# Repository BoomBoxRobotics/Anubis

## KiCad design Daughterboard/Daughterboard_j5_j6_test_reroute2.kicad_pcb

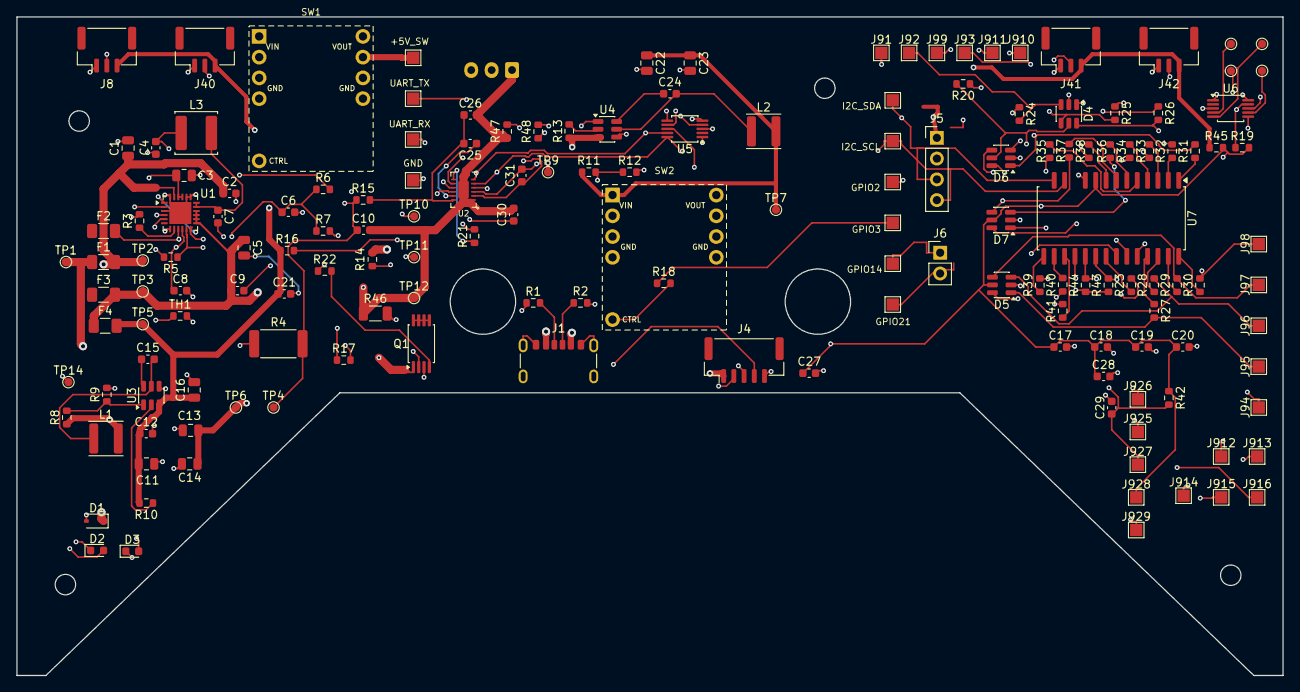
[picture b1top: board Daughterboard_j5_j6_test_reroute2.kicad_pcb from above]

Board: 4 copper layers, 155.0 x 80.6 mm, 160 parts (0 on the bottom side), 100 nets.

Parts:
C1: 10uF 10V X5R; C_0805_2012Metric
C2, C17, C19, C27, C29: 100nF 10V X7R; C_0603_1608Metric
C3, C5, C13, C14, C22, C23: 22uF 16V X5R; C_0805_2012Metric
C4, C7, C9, C10, C12, C15, C21, C24, C25, C26, C31: 100nF 16V X7R; C_0603_1608Metric
C6: 4.7uF 6.3V X5R; C_0603_1608Metric
C8: 100nF 10V X7R DNP; C_0603_1608Metric
C11, C16: 10uF 16V X5R; C_0805_2012Metric
C18, C20, C28: 1uF 10V X5R; C_0603_1608Metric
C30: 2.2uF 10V X5R; C_0603_1608Metric
D1: PESD5V0S1BA 5V VBUS TVS; D_SOD-323
D2: LED green; LED_0603_1608Metric
D3: LED blue; LED_0603_1608Metric
D4, D5, D6, D7: SRV05-4.TCT / C13612 4ch ESD; SOT-23-6
F1: BSMD1206-200-16V 2A hold polyfuse; Fuse_1206_3216Metric
F2: BSMD1206-200-16V cell1 PTC; Fuse_1206_3216Metric
F3: BSMD1206-200-16V cell2 PTC; Fuse_1206_3216Metric
F4: BSMD1206-200-16V system fuse; Fuse_1206_3216Metric
J1: USB-C 5V Sink; USB_C_Receptacle_GCT_USB4125-xx-x_6P_TopMnt_Horizontal
J4: BM05B-GHS-TBT UART JST-GH top-entry 1.25mm; JST_GH_BM05B-GHS-TBT_1x05-1MP_P1.25mm_Vertical
J5: I2C 2.54mm through-hole male header; PinHeader_1x04_P2.54mm_Vertical
J6: Deep sleep 2.54mm through-hole header; PinHeader_1x02_P2.54mm_Vertical
J7: 2S balance input JST-XH side-entry; JST_XH_S3B-XH-A_1x03_P2.50mm_Horizontal
J8: Left gimbal A JST-GH 1.25mm; JST_GH_BM03B-GHS-TBT_1x03-1MP_P1.25mm_Vertical
J30: J3P Hosyond +5V_SW solder pad; TestPoint_Pad_1.5x1.5mm
J31: J3A Hosyond UART_TX solder pad; TestPoint_Pad_1.5x1.5mm
J32: J3B Hosyond UART_RX solder pad; TestPoint_Pad_1.5x1.5mm
J33: J3C Hosyond I2C_SDA solder pad; TestPoint_Pad_1.5x1.5mm
J34: J3D Hosyond I2C_SCL solder pad; TestPoint_Pad_1.5x1.5mm
J35: J3E Hosyond GPIO2 solder pad; TestPoint_Pad_1.5x1.5mm
J36: J3F Hosyond GPIO3 solder pad; TestPoint_Pad_1.5x1.5mm
J37: J3G Hosyond GPIO14 solder pad; TestPoint_Pad_1.5x1.5mm
J38: J3H Hosyond GPIO21 solder pad; TestPoint_Pad_1.5x1.5mm
J39: J3I Hosyond GND solder pad; TestPoint_Pad_1.5x1.5mm
J40: Left gimbal B JST-GH 1.25mm; JST_GH_BM03B-GHS-TBT_1x03-1MP_P1.25mm_Vertical
J41: Right gimbal A JST-GH 1.25mm; JST_GH_BM03B-GHS-TBT_1x03-1MP_P1.25mm_Vertical
J42: Right gimbal B JST-GH 1.25mm; JST_GH_BM03B-GHS-TBT_1x03-1MP_P1.25mm_Vertical
J91: MCP23017 GPA0 solder pad; TestPoint_Pad_1.5x1.5mm
J92: MCP23017 GPA1 solder pad; TestPoint_Pad_1.5x1.5mm
J93: MCP23017 GPA2 solder pad; TestPoint_Pad_1.5x1.5mm
J94: MCP23017 GPA3 solder pad; TestPoint_Pad_1.5x1.5mm
J95: MCP23017 GPA4 solder pad; TestPoint_Pad_1.5x1.5mm
J96: MCP23017 GPA5 solder pad; TestPoint_Pad_1.5x1.5mm
J97: MCP23017 GPA6 solder pad; TestPoint_Pad_1.5x1.5mm
J98: MCP23017 GPA7 solder pad; TestPoint_Pad_1.5x1.5mm
J99: MCP23017 GPB0 solder pad; TestPoint_Pad_1.5x1.5mm
J910: MCP23017 GPB1 solder pad; TestPoint_Pad_1.5x1.5mm
J911: MCP23017 GPB2 solder pad; TestPoint_Pad_1.5x1.5mm
J912: MCP23017 GPB3 solder pad; TestPoint_Pad_1.5x1.5mm
J913: MCP23017 GPB4 solder pad; TestPoint_Pad_1.5x1.5mm
J914: MCP23017 GPB5 solder pad; TestPoint_Pad_1.5x1.5mm
J915: MCP23017 GPB6 solder pad; TestPoint_Pad_1.5x1.5mm
J916: MCP23017 GPB7 solder pad; TestPoint_Pad_1.5x1.5mm
J925: MCP23017 INTA solder pad; TestPoint_Pad_1.5x1.5mm
J926: MCP23017 INTB solder pad; TestPoint_Pad_1.5x1.5mm
J927: MCP23017 RESET solder pad; TestPoint_Pad_1.5x1.5mm
J928: MCP23017 +3V3_SW solder pad; TestPoint_Pad_1.5x1.5mm
J929: MCP23017 GND solder pad; TestPoint_Pad_1.5x1.5mm
L1: 4.7uH >=3A sat; L_APV_ANR4020
L2: 4.7uH >=2A sat; L_APV_ANR4020
L3: ANR5040T1R0M 1uH; L_APV_ANR5040
Q1: PT8810 dual N-MOSFET; TSSOP-8_4.4x3mm_P0.65mm
R1, R2: 5.1k 1%; R_0603_1608Metric
R3: 806R 1% ILIM; R_0603_1608Metric
R4: 43R 1W CBSET; R_2512_6332Metric
R5: 10k 1%; R_0603_1608Metric
R6, R7: 2.2k; R_0603_1608Metric
R8: 523k 1%; R_0603_1608Metric
R9, R12: 100k 1%; R_0603_1608Metric
R10, R13: 100k; R_0603_1608Metric
R11: 316k 1%; R_0603_1608Metric
R14, R15: 470R 1%; R_0603_1608Metric
R16, R21, R22, R23, R24, R25, R26, R27, R28, R29, R30, R31, R32, R33, R34, R35, R36, R37, R38, R47, R48: 100R; R_0603_1608Metric
R17, R18: 330R; R_0603_1608Metric
R19, R20: 4.7k; R_0603_1608Metric
R39, R40, R41, R45: 0R; R_0603_1608Metric
R42, R43, R44: 10k; R_0603_1608Metric
R46: 2mR 1% 50ppm; R_1206_3216Metric
SW1: Pololu #2808 5V switch; Pololu_2808_Raised_Header
SW2: Pololu #2808 3V3 switch; Pololu_2808_Raised_Header
TH1: NCP18XH103F03RB 10k NTC; R_0603_1608Metric
TP1: USB_VBUS test pad; TestPoint_Pad_D1.0mm
TP2: CHG_IN test pad; TestPoint_Pad_D1.0mm
TP3: PACK_P test pad; TestPoint_Pad_D1.0mm
TP4: CELL_MID test pad; TestPoint_Pad_D1.0mm
TP5: BAT_SYS test pad; TestPoint_Pad_D1.0mm
TP6: +5V test pad; TestPoint_Pad_D1.0mm
TP7: +3V3 test pad; TestPoint_Pad_D1.0mm
TP9: +3V3_SW test pad; TestPoint_Pad_D1.0mm
TP10: CHG_STAT test pad; TestPoint_Pad_D1.0mm
TP11: PG_STAT test pad; TestPoint_Pad_D1.0mm
TP12: BATT_RAW_N test pad; TestPoint_Pad_D1.0mm
TP14: GND test pad; TestPoint_Pad_D1.0mm
TP15: AIN4 test pad; TestPoint_Pad_D1.0mm
TP16: AIN5 test pad; TestPoint_Pad_D1.0mm
TP17: AIN6 test pad; TestPoint_Pad_D1.0mm
TP18: AIN7 test pad; TestPoint_Pad_D1.0mm
U1: BQ25887RGER 2S charger; Texas_RGE0024H_VQFN-24-1EP_4x4mm_P0.5mm_EP2.7x2.7mm
U2: BQ28Z610DRZR-R1; BQ28Z610_DRZ0012A_12SON_2.5x4mm_P0.5mm
U3: AP63200WU-7 5V Buck; TSOT-23-6
U4: AP63200WU-7 3V3 Buck; TSOT-23-6
U5: ADS1115IDGSR 0x48; TSSOP-10_3x3mm_P0.5mm
U6: ADS1115IDGSR 0x49; TSSOP-10_3x3mm_P0.5mm
U7: MCP23017-E/SO; SOIC-28W_7.5x17.9mm_P1.27mm_NoPads11_14

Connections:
+3V3: C22.1, C23.1, L2.2, R11.1, SW2.1, TP7.1
+3V3_SW: J5.1, J8.3, J40.3, J41.3, J42.3, R45.1, SW2.2, TP9.1
+3V3_SW_LOGIC: C17.1, C18.1, C19.1, C20.1, C27.1, C28.1, D4.5, D5.5, D6.5, D7.5, J928.1, R19.2, R20.2, R42.1, R43.1, R44.1, R45.2, U5.8, U6.1, U6.8, U7.9
+5V: C13.1, C14.1, L1.2, R8.1, SW1.1, TP6.1
+5V_SW: J4.1, J30.1, SW1.2
AIN0: J8.2, U5.4
AIN1: J40.2, U5.5
AIN2: J41.2, U5.6
AIN3: J42.2, U5.7
AIN4: TP15.1, U6.4
AIN5: TP16.1, U6.5
AIN6: TP17.1, U6.6
AIN7: TP18.1, U6.7
BATT_RAW_N: C10.2, C26.2, C30.2, J7.1, Q1.1, R46.1, R47.1, TP12.1, U2.1, U2.13
BAT_SYS: C11.1, C12.1, C16.1, C21.1, F4.2, R10.2, R13.2, R16.1, TP5.1, U3.3, U4.3
BQ_CHG: R22.1, U2.9
BQ_DSG: R21.1, U2.7
BQ_PACK: R16.2, U2.8
BQ_PBI: C30.1, U2.10
BQ_SRN: C31.1, R47.2, U2.2
BQ_SRP: C31.2, R48.2, U2.3
BST_3V3: C24.1, U4.6
BST_5V: C15.1, U3.6
BTST: C7.1, U1.12
CBSET: C8.1, R4.1, U1.10
CC1: J1.A5, R1.1
CC2: J1.B5, R2.1
CELL_MID: C9.2, C10.1, F2.2, J7.2, R4.2, R15.1, TP4.1, U1.9
CHG_IN: C1.1, C2.1, D1.1, F1.2, TP2.1, U1.23
CHG_STAT: D2.2, TP10.1, U1.2
CHG_SW: C7.2, L3.2, U1.17, U1.18
CO_GATE: Q1.4, R22.2
CTRL_3V3_SW: R18.2, SW2.4
CTRL_5V_SW: R17.2, SW1.4
DO_GATE: Q1.2, R21.2
EN_3V3: R13.1, U4.2
EN_5V: R10.1, U3.2
EXP_GPA0: D4.1, J91.1, R23.2
EXP_GPA1: D4.3, J92.1, R24.2
EXP_GPA2: D4.4, J93.1, R25.2
EXP_GPA3: D4.6, J94.1, R26.2
EXP_GPA4: D5.1, J95.1, R27.2
EXP_GPA5: D5.3, J96.1, R28.2
EXP_GPA6: D5.4, J97.1, R29.2
EXP_GPA7: D5.6, J98.1, R30.2
EXP_GPB0: D6.1, J99.1, R31.2
EXP_GPB1: D6.3, J910.1, R32.2
EXP_GPB2: D6.4, J911.1, R33.2
EXP_GPB3: D6.6, J912.1, R34.2
EXP_GPB4: D7.1, J913.1, R35.2
EXP_GPB5: D7.3, J914.1, R36.2
EXP_GPB6: D7.4, J915.1, R37.2
EXP_GPB7: D7.6, J916.1, R38.2
FB_3V3: R11.2, R12.1, U4.1
FB_5V: R8.2, R9.1, U3.1
GND: C1.2, C2.2, C3.2, C4.2, C5.2, C6.2, C8.2, C11.2, C12.2, C13.2, C14.2, C16.2, C17.2, C18.2, C19.2, C20.2, C21.2, C22.2, C23.2, C27.2, C28.2, C29.2, D1.2, D4.2, D5.2, D6.2, D7.2, J1.A12, J1.B12, J1.SH, J4.2, J4.5, J5.2, J8.1, J39.1, J40.1, J41.1, J42.1, J929.1, Q1.3, R1.2, R2.2, R3.2, R9.2, R12.2, R39.2, R40.2, R41.2, R46.2, R48.1, SW1.3, SW2.3, TH1.2, TP14.1, U1.3, U1.19, U1.20, U1.24, U1.25, U3.4, U4.4, U5.1, U5.3, U6.3, U7.10
GPIO2: J35.1, R17.1
GPIO3: J36.1, R18.1
GPIO14: J6.1, J37.1
GPIO21: J6.2, J38.1
I2C_SCL: J5.4, J34.1, R20.1, U1.5, U2.5, U5.10, U6.10, U7.12
I2C_SDA: J5.3, J33.1, R19.1, U1.4, U2.6, U5.9, U6.9, U7.13
ILIM: R3.1, U1.8
LED_CHG_A: D2.1, R6.2
LED_PGOOD_A: D3.1, R7.2
MCP_A0: R39.1, U7.15
MCP_A1: R40.1, U7.16
MCP_A2: R41.1, U7.17
MCP_GPA0: R23.1, U7.21
MCP_GPA1: R24.1, U7.22
MCP_GPA2: R25.1, U7.23
MCP_GPA3: R26.1, U7.24
MCP_GPA4: R27.1, U7.25
MCP_GPA5: R28.1, U7.26
MCP_GPA6: R29.1, U7.27
MCP_GPA7: R30.1, U7.28
MCP_GPB0: R31.1, U7.1
MCP_GPB1: R32.1, U7.2
MCP_GPB2: R33.1, U7.3
MCP_GPB3: R34.1, U7.4
MCP_GPB4: R35.1, U7.5
MCP_GPB5: R36.1, U7.6
MCP_GPB6: R37.1, U7.7
MCP_GPB7: R38.1, U7.8
MCP_INTA: J925.1, R43.2, U7.20
MCP_INTB: J926.1, R44.2, U7.19
MCP_RESET: C29.1, J927.1, R42.2, U7.18
PACK_P: C5.1, C9.1, F3.2, F4.1, J7.3, R14.1, TP3.1, U1.13, U1.14, U1.15, U1.16
PG_STAT: D3.2, TP11.1, U1.1
PMID: C3.1, C4.1, L3.1, U1.21, U1.22
PROT_VC: C25.2, C26.1, R15.2, U2.12
PROT_VDD: C25.1, R14.2, U2.11
Q1_DRAIN_COMMON: Q1.5, Q1.6, Q1.7, Q1.8
REGN: C6.1, R5.1, R6.1, R7.1, U1.11
SW_3V3: C24.2, L2.1, U4.5
SW_5V: C15.2, L1.1, U3.5
TS: R5.2, TH1.1, U1.7, U2.4
UART_RX: J4.4, J32.1
UART_TX: J4.3, J31.1
USB_VBUS: F1.1, J1.A9, J1.B9, TP1.1

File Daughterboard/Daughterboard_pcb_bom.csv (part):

"Section","Reference","Part / Value","Footprint","Nets","Notes","Purchase Link"
"USB-C input","J1","USB-C 5V Sink","Connector_USB:USB_C_Receptacle_GCT_USB4125-xx-x_6P_TopMnt_Horizontal","CC1,CC2,GND,USB_VBUS","Power-only sink; CC1/CC2 each have 5.1k Rd to GND.","https://www.digikey.com/en/products/result?keywords=GCT+USB4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"
"USB-C input","R1","5.1k 1%","Resistor_SMD:R_0603_1608Metric","CC1,GND","USB-C Rd.","https://www.digikey.com/en/products/result?keywords=5.1k+1%2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"
"USB-C input","R2","5.1k 1%","Resistor_SMD:R_0603_1608Metric","CC2,GND","USB-C Rd.","https://www.digikey.com/en/products/result?keywords=5.1k+1%2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"
"USB-C input","F1","2A hold polyfuse","Fuse:Fuse_1206_3216Metric","CHG_IN,USB_VBUS","Input fuse/polyfuse; choose exact SMD PTC/fuse current rating before layout.","https://www.digikey.com/en/products/result?keywords=2A+hold+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"
"USB-C input","D1","5V VBUS TVS","Diode_SMD:D_SOD-323","CHG_IN,GND","Place close to USB-C connector.","https://www.digikey.com/en/products/result?keywords=5V+VBUS+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"
"USB-C input","C1","10uF 10V X5R","Capacitor_SMD:C_0805_2012Metric","CHG_IN,GND","Charger input bulk.","https://www.digikey.com/en/products/result?keywords=10uF+10V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"
"USB-C input","C2","100nF 10V X7R","Capacitor_SMD:C_0603_1608Metric","CHG_IN,GND","Charger input bypass.","https://www.digikey.com/en/products/result?keywords=100nF+10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"
"2S charger","U1","BQ25887RGE 2S charger","Package_DFN_QFN:Texas_RGE0024H_VQFN-24-1EP_4x4mm_P0.5mm_EP2.7x2.7mm","BTST,CBSET,CELL_MID,CHG_IN,CHG_STAT,CHG_SW,GND,I2C_SCL,I2C_SDA,ILIM,PACK_P,PG_STAT,PMID,REGN,TS","USB 5V boost-mode charger for 2S Li-ion/LiPo with midpoint cell-balance connection.","https://www.digikey.com/en/products/result?keywords=BQ25887RGE"
"2S charger","L3","1uH >=4A sat","Inductor_SMD:L_APV_ANR5040","CHG_SW,PMID","BQ25887 boost-charge SMD inductor; finalize DCR/current from layout and charge limit.","https://www.digikey.com/en/products/result?keywords=1uH+%3E%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"
"2S charger","R3","806R 1% TBD","Resistor_SMD:R_0603_1608Metric","GND,ILIM","Input-current hardware limit target no more than 1.5A; set charge current in BQ25887 firmware/registers between 500mA and 1.5A.","https://www.digikey.com/en/products/result?keywords=0603+res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"
"2S charger","R4","TBD 1%","Resistor_SMD:R_0603_1608Metric","CBSET,GND","Cell-balance setting resistor; choose from BQ25887 datasheet.","https://www.digikey.com/en/products/result?keywords=0603+res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"
"2S charger","C3","22uF 16V X5R","Capacitor_SMD:C_0805_2012Metric","GND,PMID","PMID bulk capacitor.","https://www.digikey.com/en/products/result?keywords=22uF+16V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"
"2S charger","C4","100nF 16V X7R","Capacitor_SMD:C_0603_1608Metric","GND,PMID","PMID HF bypass.","https://www.digikey.com/en/products/result?keywords=100nF+16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"
"2S charger","C5","22uF 16V X5R","Capacitor_SMD:C_0805_2012Metric","GND,PACK_P","2S pack/BAT bulk capacitor.","https://www.digikey.com/en/products/result?keywords=22uF+16V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"
"2S charger","C6","4.7uF 6.3V X5R","Capacitor_SMD:C_0603_1608Metric","GND,REGN","REGN regulator capacitor.","https://www.digikey.com/en/products/result?keywords=4.7uF+6.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"
"2S charger","C7","100nF 16V X7R","Capacitor_SMD:C_0603_1608Metric","BTST,CHG_SW","Bootstrap capacitor.","https://www.digikey.com/en/products/result?keywords=100nF+16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"
"2S charger","C8","100nF 10V X7R","Capacitor_SMD:C_0603_1608Metric","CBSET,GND","CBSET filter placeholder; verify final requirement.","https://www.digikey.com/en/products/result?keywords=100nF+10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"
"2S charger","C9","100nF 16V X7R","Capacitor_SMD:C_0603_1608Metric","CELL_MID,PACK_P","Upper-cell sense bypass; place close to charger sense pins.","https://www.digikey.com/en/products/result?keywords=100nF+16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"
"2S charger","C10","100nF 16V X7R","Capacitor_SMD:C_0603_1608Metric","BATT_RAW_N,CELL_MID","Lower-cell raw-pack sense bypass; place close to charger/protection sense pins.","https://www.digikey.com/en/products/result?keywords=100nF+16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"
"2S charger","TH1","10k NTC","Resistor_SMD:R_0603_1608Metric","GND,TS","0603 NTC; place against or near the selected pack/cells.","https://www.digikey.com/en/products/result?keywords=10k+NTC+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"
"2S charger","R5","10k 1%","Resistor_SMD:R_0603_1608Metric","REGN,TS","TS bias; verify with selected NTC curve and BQ25887 TS thresholds.","https://www.digikey.com/en/products/result?keywords=10k+1%25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"
"2S charger","R6","2.2k","Resistor_SMD:R_0603_1608Metric","LED_CHG_A,REGN","Charge-status LED resistor.","https://www.digikey.com/en/products/result?keywords=2.2k+Res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"
"2S charger","D2","LED green","LED_SMD:LED_0603_1608Metric","CHG_STAT,LED_CHG_A","STAT open-drain LED.","https://www.digikey.com/en/products/result?keywords=LED+gree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"
"2S charger","R7","2.2k","Resistor_SMD:R_0603_1608Metric","LED_PGOOD_A,REGN","Power-good LED resistor.","https://www.digikey.com/en/products/result?keywords=2.2k+Res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"
"2S charger","D3","LED blue","LED_SMD:LED_0603_1608Metric","LED_PGOOD_A,PG_STAT","PG open-drain LED.","https://www.digikey.com/en/products/result?keywords=LED+blue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"
"Battery","BT1","18650 Cell 1 lower","","BATT_RAW_N,CELL1_P","Lower series cell holder: negative to raw pack negative, positive through F2 to CELL_MID.","https://www.digikey.com/en/products/result?keywords=18650+ba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"
"Battery","BT2","18650 Cell 2 upper","","CELL2_P,CELL_MID","Upper series cell holder: negative to CELL_MID, positive through F3 to PACK_P.","https://www.digikey.com/en/products/result?keywords=18650+ba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"
"Battery","F2","PTC/fuse cell1","Fuse:Fuse_1206_3216Metric","CELL1_P,CELL_MID","SMD cell fuse/PTC; place close to lower cell positive.","https://www.digikey.com/en/products/result?keywords=PTC%2Ffu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"
"Battery","F3","PTC/fuse cell2","Fuse:Fuse_1206_3216Metric","CELL2_P,PACK_P","SMD cell fuse/PTC; place close to upper cell positive.","https://www.digikey.com/en/products/result?keywords=PTC%2Ffu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"
"Battery","J7","2S balance input JST-XH side-entry","Connector_JST:JST_XH_S3B-XH-A_1x03_P2.50mm_Horizontal","BATT_RAW_N,CELL_MID,PACK_P","Top-edge side-entry 2S balance connector pinout: B-, cell midpoint, B+. Pin 1 is raw pack negative before protection FETs.","https://www.digikey.com/en/products/result?keywords=JST+XH+3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"
"2S protection","U2","BQ28Z610DRZR-R1","Daughterboard:BQ28Z610_DRZ0012A_12SON_2.5x4mm_P0.5mm","BATT_RAW_N,BQ_CHG,BQ_DSG,BQ_PACK,BQ_PBI,BQ_SRN,BQ_SRP,I2C_SCL,I2C_SDA,PROT_VC,PROT_VDD,TS","TI 1S/2S gas gauge and primary protection controller. Requires BQStudio/data-flash setup; verify final FET topology before fabrication.","https://www.digikey.com/en/products/detail/texas-instruments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"
"2S protection","R14","470R 1%","Resistor_SMD:R_0603_1608Metric","PACK_P,PROT_VDD","BQ28Z610 VC2 input resistor; place near U2 and verify with cell-balance routing.","https://www.digikey.com/en/products/result?keywords=470R+1%2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"
"2S protection","R15","470R 1%","Resistor_SMD:R_0603_1608Metric","CELL_MID,PROT_VC","BQ28Z610 VC1 input resistor; place near U2 and verify with cell-balance routing.","https://www.digikey.com/en/products/result?keywords=470R+1%2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"
"2S protection","C25","100nF 16V X7R","Capacitor_SMD:C_0603_1608Metric","PROT_VC,PROT_VDD","BQ28Z610 upper-cell sense filter capacitor.","https://www.digikey.com/en/products/result?keywords=100nF+16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"
"2S protection","C26","100nF 16V X7R","Capacitor_SMD:C_0603_1608Metric","BATT_RAW_N,PROT_VC","BQ28Z610 lower-cell sense filter capacitor.","https://www.digikey.com/en/products/result?keywords=100nF+16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"
"2S protection","R16","100R","Resistor_SMD:R_0603_1608Metric","BAT_SYS,BQ_PACK","BQ28Z610 PACK input series resistor; verify final pack/system-side node after FET topology review.","https://www.digikey.com/en/products/result?keywords=100R+Res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"
"2S protection","C30","2.2uF 10V X5R","Capacitor_SMD:C_0603_1608Metric","BATT_RAW_N,BQ_PBI","BQ28Z610 PBI hold-up capacitor; place close to U2.","https://www.digikey.com/en/products/result?keywords=2.2uF+10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"
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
